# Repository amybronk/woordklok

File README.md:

# woordklok
het is een woordklok
 de dezine files moeten nog geupload worden

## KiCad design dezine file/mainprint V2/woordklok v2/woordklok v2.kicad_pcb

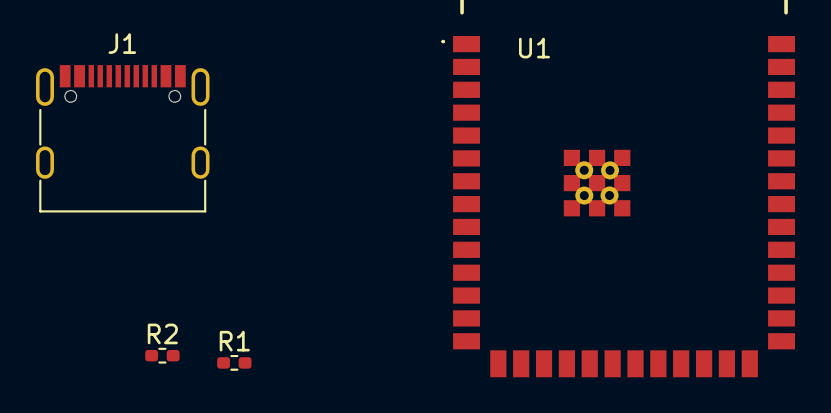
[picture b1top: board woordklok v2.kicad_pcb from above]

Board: 2 copper layers, 4 parts (0 on the bottom side), 6 nets, no tracks yet.

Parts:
J1: USB_C_Receptacle_USB2.0_16P; USB_C_Receptacle_G-Switch_GT-USB-7010ASV
R1, R2: 22R; R_0402_1005Metric_Pad0.72x0.64mm_HandSolder
U1: esp32-s3-wroom; ESP32S3WROOM1

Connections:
/USB1.D+: R2.1, U1.14 (IO20)
/USB1.D-: R1.1, U1.13 (IO19)
GND: J1.A1 (GND), J1.A12 (GND), J1.B1 (GND), J1.B12 (GND), J1.S1 (SHIELD), U1.1 (GND), U1.40 (GND), U1.41 (GND)
unnamed: J1.A4 (VBUS), J1.A9 (VBUS), J1.B4 (VBUS), J1.B9 (VBUS)
USB_N: J1.A7 (D-), J1.B7 (D-), R1.2
USB_P: J1.A6 (D+), J1.B6 (D+), R2.2

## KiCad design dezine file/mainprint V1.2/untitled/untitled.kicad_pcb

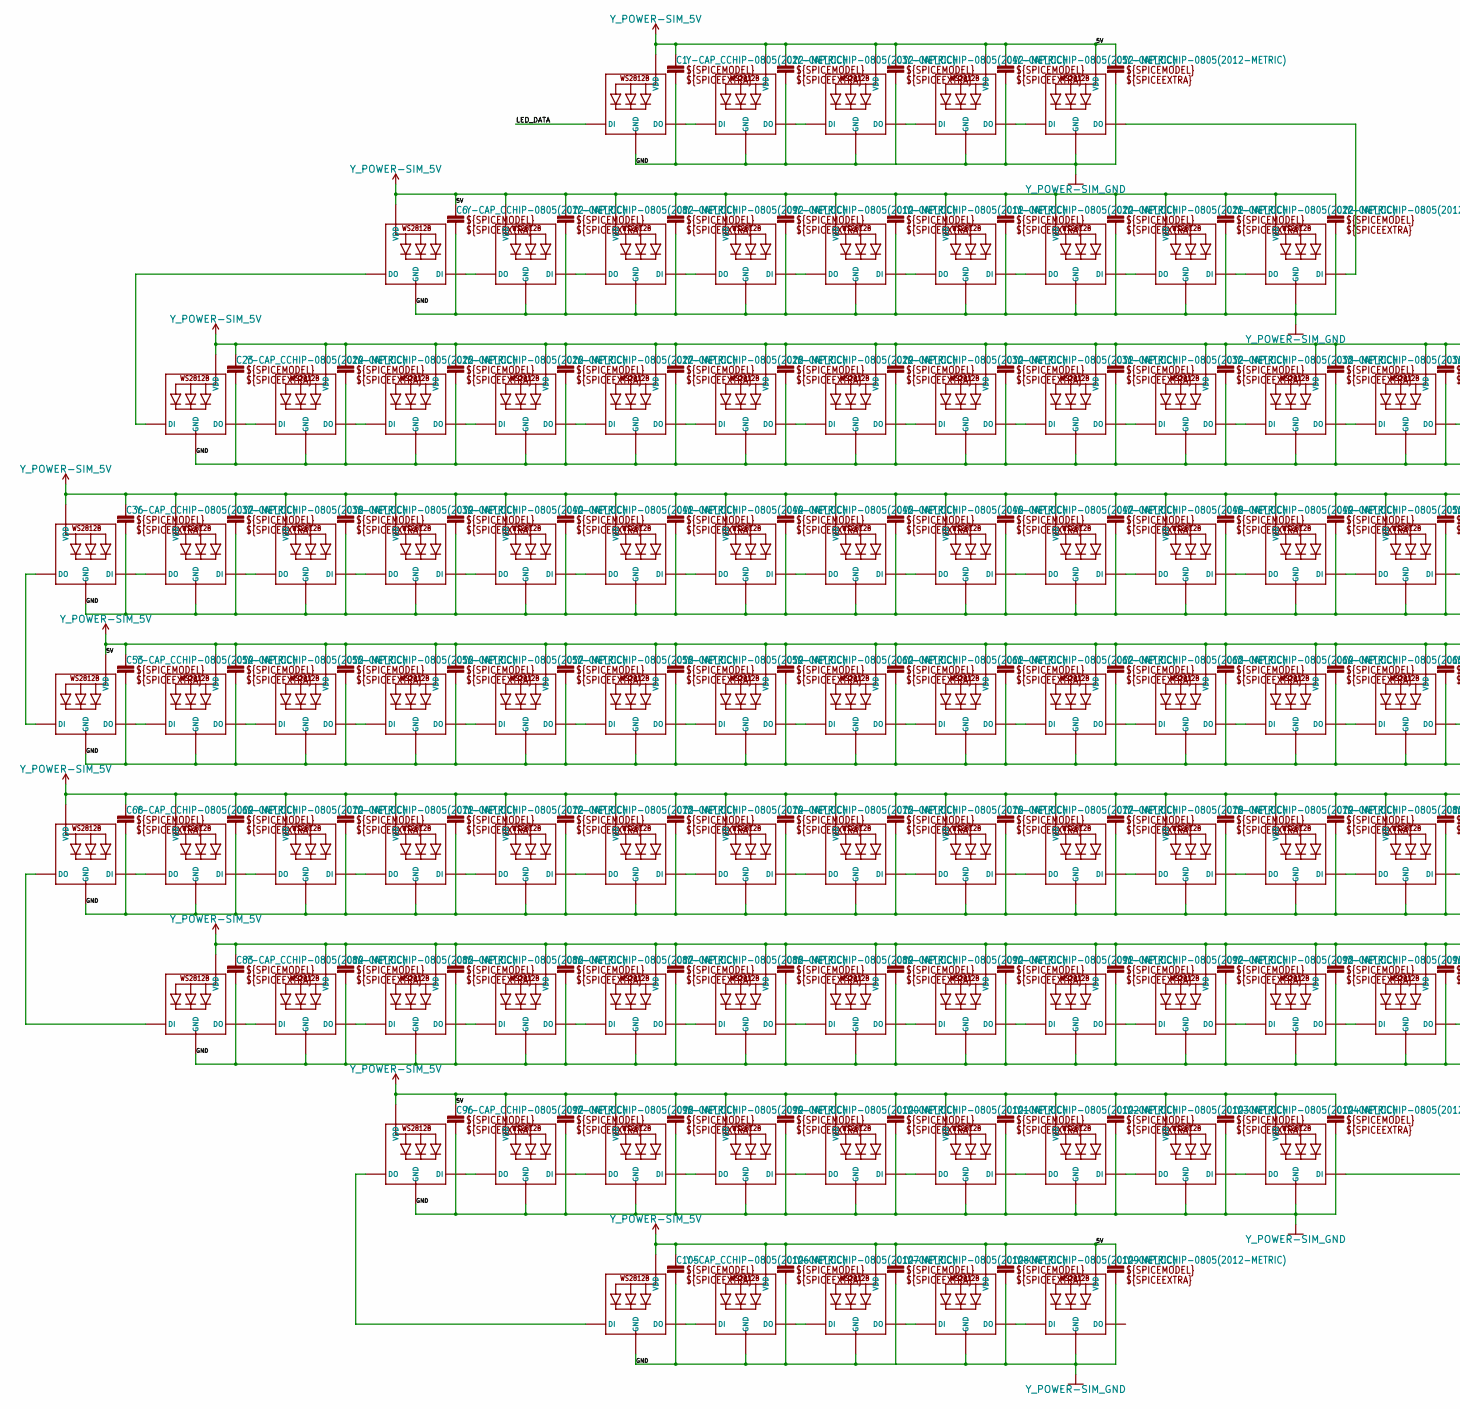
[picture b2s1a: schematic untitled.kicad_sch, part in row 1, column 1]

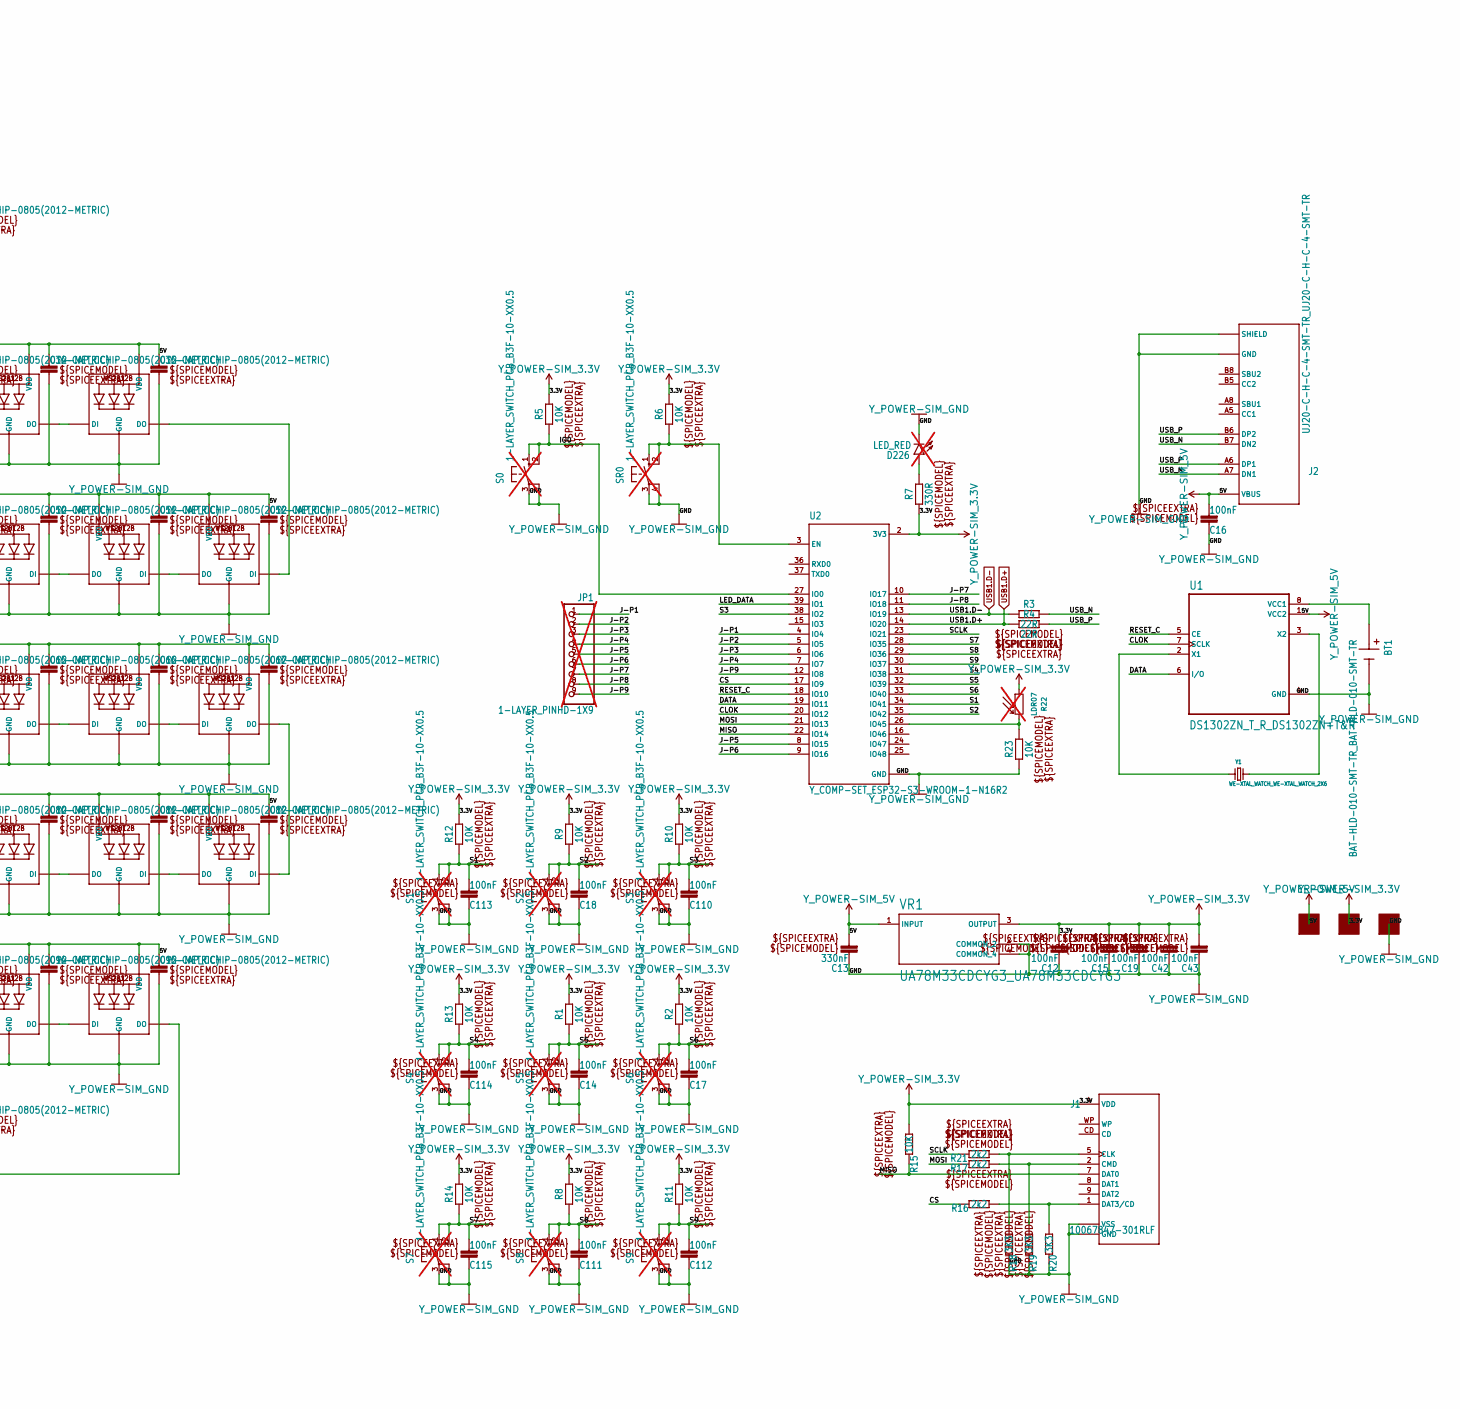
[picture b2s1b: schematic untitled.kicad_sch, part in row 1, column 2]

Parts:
BT1: BAT-HLD-010-SMT-TR_BAT-HLD-010-SMT-TR; BAT-HLD-010-SMT-TR_BAT_BAT-HLD-010-SMT-TR
C1, C2, C3, C4, C5, C6, C7, C8, C9, C10, C11, C20, C21, C22, C23, C24, C25, C26, C27, C28, C29, C30, C31, C32, C33, C34, C35, C36, C37, C38, C39, C40, C41, C44, C45, C46, C47, C48, C49, C50, C51, C52, C53, C54, C55, C56, C57, C58, C59, C60, C61, C62, C63, C64, C65, C66, C67, C68, C69, C70, C71, C72, C73, C74, C75, C76, C77, C78, C79, C80, C81, C82, C83, C84, C85, C86, C87, C88, C89, C90, C91, C92, C93, C94, C95, C96, C97, C98, C99, C100, C101, C102, C103, C104, C105, C106, C107, C108, C109: Y-CAP_CCHIP-0805(2012-METRIC); Y-CAP_CAPC2012X110
C12, C14, C15, C16, C17, C18, C19, C42, C43, C110, C111, C112, C113, C114, C115: 100nF; Y-CAP_CAPC2012X110
C13: 330nF; Y-CAP_CAPC2012X110
D226: LED_RED; 1-LAYER_LED5MM_R-ROC; not fitted
J1: 10067847-301RLF; AMPHENOL_10067847-301RLF
J2: UJ20-C-H-C-4-SMT-TR_UJ20-C-H-C-4-SMT-TR; UJ20-C-H-C-4-SMT-TR_CUI_UJ20-C-H-C-4-SMT-TR
JP1: 1-LAYER_PINHD-1X9; 1-LAYER_1X09; not fitted
LED1, LED2, LED3, LED4, LED5, LED6, LED7, LED8, LED9, LED10, LED11, LED12, LED13, LED14, LED15, LED16, LED17, LED18, LED19, LED20, LED21, LED22, LED23, LED24, LED25, LED26, LED27, LED28, LED29, LED30, LED31, LED32, LED33, LED34, LED35, LED36, LED37, LED38, LED39, LED40, LED41, LED42, LED43, LED44, LED45, LED46, LED47, LED48, LED49, LED50, LED51, LED52, LED53, LED54, LED55, LED56, LED57, LED58, LED59, LED60, LED61, LED62, LED63, LED64, LED65, LED66, LED67, LED68, LED69, LED70, LED71, LED72, LED73, LED74, LED75, LED76, LED77, LED78, LED79, LED80, LED81, LED82, LED83, LED84, LED85, LED86, LED87, LED88, LED89, LED90, LED91, LED92, LED93, LED94, LED95, LED96, LED97, LED98, LED99: WS2812B_WS2812B_5050N; WS2812B_WS2812B-NARROW
R1, R2, R5, R6, R8, R9, R10, R11, R12, R13, R14, R15, R23: 10K; Y-RES_RESC2012X65
R3, R4: 22R; Y-RES_RESC2012X65
R7: 330R; Y-RES_RESC2012X65
R16, R17, R21: 2k2; Y-RES_RESC2012X65
R18, R19, R20: 3K3; Y-RES_RESC2012X65
R22: LDR07; R_LDR_5.1x4.3mm_P3.4mm_Vertical; not fitted
S0, S1, S2, S3, S4, S5, S6, S7, S8, S9: 1-LAYER_SWITCH_PCB_B3F-10-XX0.5; 1-LAYER_B3F-10XXROC; not fitted
SR0: 1-LAYER_SWITCH_PCB_B3F-10-XX0.5; 1-LAYER_B3F-10XXROC; not fitted
U1: DS1302ZN_T_R_DS1302ZN+T&R; DS1302ZN_T_R_SOIC127P600X175-8N
U2: Y_COMP-SET_ESP32-S3-WROOM-1-N16R2; Y_COMP-SET_XCVR_ESP32-S3-WROOM-1-N16R2
U$1, U$2, U$3: Y_CONECTOR_POGOPAD2; Y_CONECTOR_POGOPAD_50
VR1: UA78M33CDCYG3_UA78M33CDCYG3; UA78M33CDCYG3_VREG_UA78M33CDCYG3
Y1: WE-XTAL_WATCH_WE-XTAL_WATCH_2X6; WE-XTAL_WATCH_WE-XTAL_WATCH-2X6

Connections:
/CLOK: U1.7 (SCLK), U2.20 (IO12)
/CS: R16.2, U2.17 (IO9)
/DATA: U1.6 (I/O), U2.19 (IO11)
/IO0: R5.1, S0.1 (S), S0.2 (S1), U2.27 (IO0)
/J-P1: JP1.1, U2.4 (IO4)
/J-P2: JP1.2, U2.5 (IO5)
/J-P3: JP1.3, U2.6 (IO6)
/J-P4: JP1.4, U2.7 (IO7)
/J-P5: JP1.5, U2.8 (IO15)
/J-P6: JP1.6, U2.9 (IO16)
/J-P7: JP1.7, U2.10 (IO17)
/J-P8: JP1.8, U2.11 (IO18)
/J-P9: JP1.9, U2.12 (IO8)
/LED_DATA: LED1.4-DIN (DI), U2.39 (IO1)
/MISO: J1.7 (DAT0), R15.2, U2.22 (IO14)
/MOSI: R17.2, U2.21 (IO13)
/RESET_C: U1.5 (CE), U2.18 (IO10)
/S1: C113.2, R12.1, S1.1 (S), S1.2 (S1), U2.34 (IO41)
/S2: C18.2, R9.1, S2.1 (S), S2.2 (S1), U2.35 (IO42)
/S3: C110.2, R10.1, S3.1 (S), S3.2 (S1), U2.38 (IO2)
/S4: C114.2, R13.1, S4.1 (S), S4.2 (S1), U2.31 (IO38)
/S5: C14.2, R1.1, S5.1 (S), S5.2 (S1), U2.32 (IO39)
/S6: C17.2, R2.1, S6.1 (S), S6.2 (S1), U2.33 (IO40)
/S7: C115.2, R14.1, S7.1 (S), S7.2 (S1), U2.28 (IO35)
/S8: C111.2, R8.1, S8.1 (S), S8.2 (S1), U2.29 (IO36)
/S9: C112.2, R11.1, S9.1 (S), S9.2 (S1), U2.30 (IO37)
/SCLK: R21.2, U2.23 (IO21)
/USB_N: J2.A7 (DN1), J2.B7 (DN2), R3.2
/USB_P: J2.A6 (DP1), J2.B6 (DP2), R4.2
unnamed: J1.5 (CLK), R18.1, R21.1
unnamed: J1.2 (CMD), R17.1, R19.1
unnamed: J1.1 (DAT3/CD), R16.1, R20.1
unnamed: LED1.2-DOUT (DO), LED2.4-DIN (DI)
unnamed: LED2.2-DOUT (DO), LED3.4-DIN (DI)
unnamed: LED3.2-DOUT (DO), LED4.4-DIN (DI)
unnamed: LED4.2-DOUT (DO), LED5.4-DIN (DI)
unnamed: LED6.4-DIN (DI), LED7.2-DOUT (DO)
unnamed: LED7.4-DIN (DI), LED8.2-DOUT (DO)
unnamed: LED8.4-DIN (DI), LED9.2-DOUT (DO)
unnamed: LED10.4-DIN (DI), LED11.2-DOUT (DO)
unnamed: LED9.4-DIN (DI), LED10.2-DOUT (DO)
unnamed: LED11.4-DIN (DI), LED12.2-DOUT (DO)
unnamed: LED12.4-DIN (DI), LED13.2-DOUT (DO)
unnamed: LED13.4-DIN (DI), LED14.2-DOUT (DO)
unnamed: LED5.2-DOUT (DO), LED14.4-DIN (DI)
unnamed: LED15.4-DIN (DI), LED24.2-DOUT (DO)
unnamed: LED15.2-DOUT (DO), LED26.4-DIN (DI)
unnamed: LED16.4-DIN (DI), LED17.2-DOUT (DO)
unnamed: LED16.2-DOUT (DO), LED27.4-DIN (DI)
unnamed: LED17.4-DIN (DI), LED18.2-DOUT (DO)
unnamed: LED18.4-DIN (DI), LED19.2-DOUT (DO)
unnamed: LED19.4-DIN (DI), LED25.2-DOUT (DO)
unnamed: LED6.2-DOUT (DO), LED20.4-DIN (DI)
unnamed: LED20.2-DOUT (DO), LED21.4-DIN (DI)
unnamed: LED21.2-DOUT (DO), LED22.4-DIN (DI)
unnamed: LED22.2-DOUT (DO), LED23.4-DIN (DI)
unnamed: LED23.2-DOUT (DO), LED24.4-DIN (DI)
unnamed: LED25.4-DIN (DI), LED45.2-DOUT (DO)
unnamed: LED26.2-DOUT (DO), LED32.4-DIN (DI)
unnamed: LED27.2-DOUT (DO), LED28.4-DIN (DI)
unnamed: LED28.2-DOUT (DO), LED29.4-DIN (DI)
unnamed: LED29.2-DOUT (DO), LED30.4-DIN (DI)
unnamed: LED30.2-DOUT (DO), LED31.4-DIN (DI)
unnamed: LED31.2-DOUT (DO), LED50.4-DIN (DI)
unnamed: LED32.2-DOUT (DO), LED38.4-DIN (DI)
unnamed: LED33.4-DIN (DI), LED34.2-DOUT (DO)
unnamed: LED33.2-DOUT (DO), LED73.4-DIN (DI)
unnamed: LED34.4-DIN (DI), LED35.2-DOUT (DO)
unnamed: LED35.4-DIN (DI), LED36.2-DOUT (DO)
unnamed: LED36.4-DIN (DI), LED37.2-DOUT (DO)
unnamed: LED37.4-DIN (DI), LED39.2-DOUT (DO)
unnamed: LED38.2-DOUT (DO), LED44.4-DIN (DI)
unnamed: LED39.4-DIN (DI), LED40.2-DOUT (DO)
unnamed: LED40.4-DIN (DI), LED41.2-DOUT (DO)
unnamed: LED41.4-DIN (DI), LED42.2-DOUT (DO)
unnamed: LED42.4-DIN (DI), LED43.2-DOUT (DO)
unnamed: LED43.4-DIN (DI), LED58.2-DOUT (DO)
unnamed: LED44.2-DOUT (DO), LED55.4-DIN (DI)
unnamed: LED45.4-DIN (DI), LED46.2-DOUT (DO)
unnamed: LED46.4-DIN (DI), LED47.2-DOUT (DO)
unnamed: LED47.4-DIN (DI), LED48.2-DOUT (DO)
unnamed: LED48.4-DIN (DI), LED49.2-DOUT (DO)
unnamed: LED49.4-DIN (DI), LED60.2-DOUT (DO)
unnamed: LED50.2-DOUT (DO), LED51.4-DIN (DI)
unnamed: LED51.2-DOUT (DO), LED52.4-DIN (DI)
unnamed: LED52.2-DOUT (DO), LED53.4-DIN (DI)
unnamed: LED53.2-DOUT (DO), LED54.4-DIN (DI)
unnamed: LED54.2-DOUT (DO), LED65.4-DIN (DI)
unnamed: LED55.2-DOUT (DO), LED56.4-DIN (DI)
unnamed: LED56.2-DOUT (DO), LED57.4-DIN (DI)
unnamed: LED57.2-DOUT (DO), LED69.4-DIN (DI)
unnamed: LED58.4-DIN (DI), LED59.2-DOUT (DO)
unnamed: LED59.4-DIN (DI), LED63.2-DOUT (DO)
unnamed: LED60.4-DIN (DI), LED61.2-DOUT (DO)
unnamed: LED61.4-DIN (DI), LED62.2-DOUT (DO)
unnamed: LED62.4-DIN (DI), LED68.2-DOUT (DO)
unnamed: LED63.4-DIN (DI), LED64.2-DOUT (DO)
unnamed: LED64.4-DIN (DI), LED72.2-DOUT (DO)
unnamed: LED65.2-DOUT (DO), LED66.4-DIN (DI)
unnamed: LED66.2-DOUT (DO), LED67.4-DIN (DI)
unnamed: LED67.2-DOUT (DO), LED70.4-DIN (DI)
unnamed: LED68.4-DIN (DI), LED69.2-DOUT (DO)
unnamed: LED70.2-DOUT (DO), LED71.4-DIN (DI)
unnamed: LED71.2-DOUT (DO), LED72.4-DIN (DI)
unnamed: LED73.2-DOUT (DO), LED74.4-DIN (DI)
unnamed: LED74.2-DOUT (DO), LED75.4-DIN (DI)
unnamed: LED75.2-DOUT (DO), LED76.4-DIN (DI)
unnamed: LED76.2-DOUT (DO), LED77.4-DIN (DI)
unnamed: LED77.2-DOUT (DO), LED78.4-DIN (DI)
unnamed: LED78.2-DOUT (DO), LED79.4-DIN (DI)
unnamed: LED79.2-DOUT (DO), LED80.4-DIN (DI)
unnamed: LED80.2-DOUT (DO), LED81.4-DIN (DI)
unnamed: LED81.2-DOUT (DO), LED82.4-DIN (DI)
unnamed: LED82.2-DOUT (DO), LED83.4-DIN (DI)
unnamed: LED83.2-DOUT (DO), LED84.4-DIN (DI)
unnamed: LED84.2-DOUT (DO), LED85.4-DIN (DI)
unnamed: LED85.2-DOUT (DO), LED94.4-DIN (DI)
unnamed: LED86.4-DIN (DI), LED87.2-DOUT (DO)
unnamed: LED86.2-DOUT (DO), LED95.4-DIN (DI)
unnamed: LED87.4-DIN (DI), LED88.2-DOUT (DO)
unnamed: LED88.4-DIN (DI), LED89.2-DOUT (DO)
unnamed: LED89.4-DIN (DI), LED90.2-DOUT (DO)
unnamed: LED90.4-DIN (DI), LED91.2-DOUT (DO)
unnamed: LED91.4-DIN (DI), LED92.2-DOUT (DO)
unnamed: LED92.4-DIN (DI), LED93.2-DOUT (DO)
unnamed: LED93.4-DIN (DI), LED94.2-DOUT (DO)
unnamed: LED95.2-DOUT (DO), LED96.4-DIN (DI)
unnamed: LED96.2-DOUT (DO), LED97.4-DIN (DI)
unnamed: LED97.2-DOUT (DO), LED98.4-DIN (DI)
unnamed: LED98.2-DOUT (DO), LED99.4-DIN (DI)
unnamed: R6.1, SR0.1 (S), SR0.2 (S1), U2.3 (EN)
unnamed: BT1.P, U1.8 (VCC1)
unnamed: U1.2 (X1), Y1.1
unnamed: U1.3 (X2), Y1.2
unnamed: R22.2, R23.2, U2.26 (IO45)
USB1.D+: R4.1, U2.14 (IO20)
USB1.D-: R3.1, U2.13 (IO19)
Y_POWER-SIM_3.3V: C12.2, C15.2, C19.2, C42.2, C43.2, J1.4 (VDD), R1.2, R2.2, R5.2, R6.2, R7.1, R8.2, R9.2, R10.2, R11.2, R12.2, R13.2, R14.2, R15.1, R22.1, U2.2 (3V3), U$1.P$1, VR1.3 (OUTPUT)
Y_POWER-SIM_5V: C1.1, C2.1, C3.1, C4.1, C5.1, C6.1, C7.1, C8.1, C9.1, C10.1, C11.1, C13.2, C16.2, C20.1, C21.1, C22.1, C23.1, C24.1, C25.1, C26.1, C27.1, C28.1, C29.1, C30.1, C31.1, C32.1, C33.1, C34.1, C35.1, C36.1, C37.1, C38.1, C39.1, C40.1, C41.1, C44.1, C45.1, C46.1, C47.1, C48.1, C49.1, C50.1, C51.1, C52.1, C53.1, C54.1, C55.1, C56.1, C57.1, C58.1, C59.1, C60.1, C61.1, C62.1, C63.1, C64.1, C65.1, C66.1, C67.1, C68.1, C69.1, C70.1, C71.1, C72.1, C73.1, C74.1, C75.1, C76.1, C77.1, C78.1, C79.1, C80.1, C81.1, C82.1, C83.1, C84.1, C85.1, C86.1, C87.1, C88.1, C89.1, C90.1, C91.1, C92.1, C93.1, C94.1, C95.1, C96.1, C97.1, C98.1, C99.1, C100.1, C101.1, C102.1, C103.1, C104.1, C105.1, C106.1, C107.1, C108.1, C109.1, J2.A4_B9 (VBUS), J2.A9_B4 (VBUS), LED1.1-VDD (VDD), LED2.1-VDD (VDD), LED3.1-VDD (VDD), LED4.1-VDD (VDD), LED5.1-VDD (VDD), LED6.1-VDD (VDD), LED7.1-VDD (VDD), LED8.1-VDD (VDD), LED9.1-VDD (VDD), LED10.1-VDD (VDD), LED11.1-VDD (VDD), LED12.1-VDD (VDD), LED13.1-VDD (VDD), LED14.1-VDD (VDD), LED15.1-VDD (VDD), LED16.1-VDD (VDD), LED17.1-VDD (VDD), LED18.1-VDD (VDD), LED19.1-VDD (VDD), LED20.1-VDD (VDD), LED21.1-VDD (VDD), LED22.1-VDD (VDD), LED23.1-VDD (VDD), LED24.1-VDD (VDD), LED25.1-VDD (VDD), LED26.1-VDD (VDD), LED27.1-VDD (VDD), LED28.1-VDD (VDD), LED29.1-VDD (VDD), LED30.1-VDD (VDD), LED31.1-VDD (VDD), LED32.1-VDD (VDD), LED33.1-VDD (VDD), LED34.1-VDD (VDD), LED35.1-VDD (VDD), LED36.1-VDD (VDD), LED37.1-VDD (VDD), LED38.1-VDD (VDD), LED39.1-VDD (VDD), LED40.1-VDD (VDD), LED41.1-VDD (VDD), LED42.1-VDD (VDD), LED43.1-VDD (VDD), LED44.1-VDD (VDD), LED45.1-VDD (VDD), LED46.1-VDD (VDD), LED47.1-VDD (VDD), LED48.1-VDD (VDD), LED49.1-VDD (VDD), LED50.1-VDD (VDD), LED51.1-VDD (VDD), LED52.1-VDD (VDD), LED53.1-VDD (VDD), LED54.1-VDD (VDD), LED55.1-VDD (VDD), LED56.1-VDD (VDD), LED57.1-VDD (VDD), LED58.1-VDD (VDD), LED59.1-VDD (VDD), LED60.1-VDD (VDD), LED61.1-VDD (VDD), LED62.1-VDD (VDD), LED63.1-VDD (VDD), LED64.1-VDD (VDD), LED65.1-VDD (VDD), LED66.1-VDD (VDD), LED67.1-VDD (VDD), LED68.1-VDD (VDD), LED69.1-VDD (VDD), LED70.1-VDD (VDD), LED71.1-VDD (VDD), LED72.1-VDD (VDD), LED73.1-VDD (VDD), LED74.1-VDD (VDD), LED75.1-VDD (VDD), LED76.1-VDD (VDD), LED77.1-VDD (VDD), LED78.1-VDD (VDD), LED79.1-VDD (VDD), LED80.1-VDD (VDD), LED81.1-VDD (VDD), LED82.1-VDD (VDD), LED83.1-VDD (VDD), LED84.1-VDD (VDD), LED85.1-VDD (VDD), LED86.1-VDD (VDD), LED87.1-VDD (VDD), LED88.1-VDD (VDD), LED89.1-VDD (VDD), LED90.1-VDD (VDD), LED91.1-VDD (VDD), LED92.1-VDD (VDD), LED93.1-VDD (VDD), LED94.1-VDD (VDD), LED95.1-VDD (VDD), LED96.1-VDD (VDD), LED97.1-VDD (VDD), LED98.1-VDD (VDD), LED99.1-VDD (VDD), U1.1 (VCC2), U$3.P$1, VR1.1 (INPUT)
Y_POWER-SIM_GND: BT1.N, C1.2, C2.2, C3.2, C4.2, C5.2, C6.2, C7.2, C8.2, C9.2, C10.2, C11.2, C12.1, C13.1, C14.1, C15.1, C16.1, C17.1, C18.1, C19.1, C20.2, C21.2, C22.2, C23.2, C24.2, C25.2, C26.2, C27.2, C28.2, C29.2, C30.2, C31.2, C32.2, C33.2, C34.2, C35.2, C36.2, C37.2, C38.2, C39.2, C40.2, C41.2, C42.1, C43.1, C44.2, C45.2, C46.2, C47.2, C48.2, C49.2, C50.2, C51.2, C52.2, C53.2, C54.2, C55.2, C56.2, C57.2, C58.2, C59.2, C60.2, C61.2, C62.2, C63.2, C64.2, C65.2, C66.2, C67.2, C68.2, C69.2, C70.2, C71.2, C72.2, C73.2, C74.2, C75.2, C76.2, C77.2, C78.2, C79.2, C80.2, C81.2, C82.2, C83.2, C84.2, C85.2, C86.2, C87.2, C88.2, C89.2, C90.2, C91.2, C92.2, C93.2, C94.2, C95.2, C96.2, C97.2, C98.2, C99.2, C100.2, C101.2, C102.2, C103.2, C104.2, C105.2, C106.2, C107.2, C108.2, C109.2, C110.1, C111.1, C112.1, C113.1, C114.1, C115.1, D226.2 (C), J1.3 (VSS), J1.6 (VSS), J1.G1 (GND), J1.G2 (GND), J2.A1_B12 (GND), J2.A12_B1 (GND), J2.SH1 (SHIELD), J2.SH2 (SHIELD), J2.SH3 (SHIELD), J2.SH4 (SHIELD), LED1.3-GND (GND), LED2.3-GND (GND), LED3.3-GND (GND), LED4.3-GND (GND), LED5.3-GND (GND), LED6.3-GND (GND), LED7.3-GND (GND), LED8.3-GND (GND), LED9.3-GND (GND), LED10.3-GND (GND), LED11.3-GND (GND), LED12.3-GND (GND), LED13.3-GND (GND), LED14.3-GND (GND), LED15.3-GND (GND), LED16.3-GND (GND), LED17.3-GND (GND), LED18.3-GND (GND), LED19.3-GND (GND), LED20.3-GND (GND), LED21.3-GND (GND), LED22.3-GND (GND), LED23.3-GND (GND), LED24.3-GND (GND), LED25.3-GND (GND), LED26.3-GND (GND), LED27.3-GND (GND), LED28.3-GND (GND), LED29.3-GND (GND), LED30.3-GND (GND), LED31.3-GND (GND), LED32.3-GND (GND), LED33.3-GND (GND), LED34.3-GND (GND), LED35.3-GND (GND), LED36.3-GND (GND), LED37.3-GND (GND), LED38.3-GND (GND), LED39.3-GND (GND), LED40.3-GND (GND), LED41.3-GND (GND), LED42.3-GND (GND), LED43.3-GND (GND), LED44.3-GND (GND), LED45.3-GND (GND), LED46.3-GND (GND), LED47.3-GND (GND), LED48.3-GND (GND), LED49.3-GND (GND), LED50.3-GND (GND), LED51.3-GND (GND), LED52.3-GND (GND), LED53.3-GND (GND), LED54.3-GND (GND), LED55.3-GND (GND), LED56.3-GND (GND), LED57.3-GND (GND), LED58.3-GND (GND), LED59.3-GND (GND), LED60.3-GND (GND), LED61.3-GND (GND), LED62.3-GND (GND), LED63.3-GND (GND), LED64.3-GND (GND), LED65.3-GND (GND), LED66.3-GND (GND), LED67.3-GND (GND), LED68.3-GND (GND), LED69.3-GND (GND), LED70.3-GND (GND), LED71.3-GND (GND), LED72.3-GND (GND), LED73.3-GND (GND), LED74.3-GND (GND), LED75.3-GND (GND), LED76.3-GND (GND), LED77.3-GND (GND), LED78.3-GND (GND), LED79.3-GND (GND), LED80.3-GND (GND), LED81.3-GND (GND), LED82.3-GND (GND), LED83.3-GND (GND), LED84.3-GND (GND), LED85.3-GND (GND), LED86.3-GND (GND), LED87.3-GND (GND), LED88.3-GND (GND), LED89.3-GND (GND), LED90.3-GND (GND), LED91.3-GND (GND), LED92.3-GND (GND), LED93.3-GND (GND), LED94.3-GND (GND), LED95.3-GND (GND), LED96.3-GND (GND), LED97.3-GND (GND), LED98.3-GND (GND), LED99.3-GND (GND), R18.2, R19.2, R20.2, R23.1, S0.3, S0.4 (P1), S1.3, S1.4 (P1), S2.3, S2.4 (P1), S3.3, S3.4 (P1), S4.3, S4.4 (P1), S5.3, S5.4 (P1), S6.3, S6.4 (P1), S7.3, S7.4 (P1), S8.3, S8.4 (P1), S9.3, S9.4 (P1), SR0.3, SR0.4 (P1), U1.4 (GND), U2.1 (GND), U2.40 (GND), U2.41_1 (GND), U2.41_2 (GND), U2.41_3 (GND), U2.41_4 (GND), U2.41_5 (GND), U2.41_6 (GND), U2.41_7 (GND), U2.41_8 (GND), U2.41_9 (GND), U2.41_10 (GND), U2.41_11 (GND), U2.41_12 (GND), U2.41_13 (GND), U2.41_14 (GND), U2.41_15 (GND), U2.41_16 (GND), U2.41_17 (GND), U2.41_18 (GND), U2.41_19 (GND), U2.41_20 (GND), U2.41_21 (GND), U$2.P$1, VR1.2 (COMMON_2), VR1.4 (COMMON_4)

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
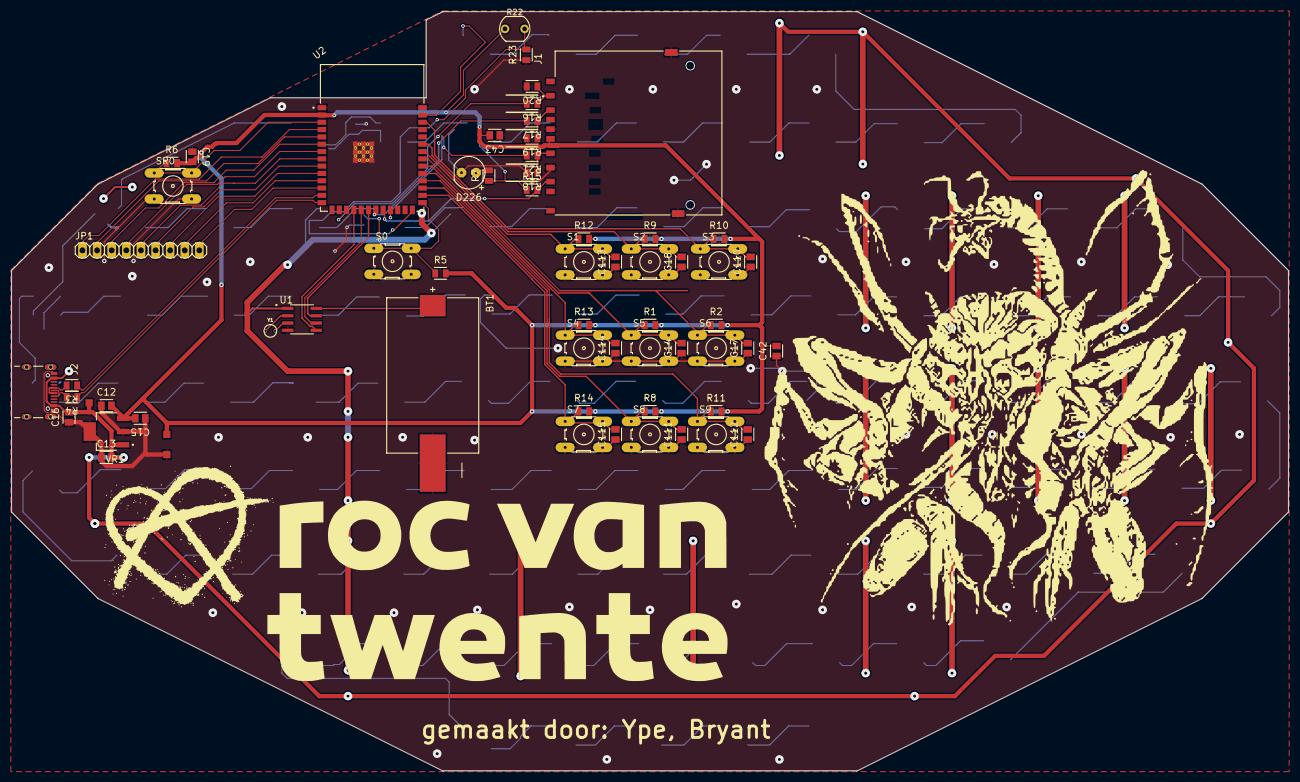
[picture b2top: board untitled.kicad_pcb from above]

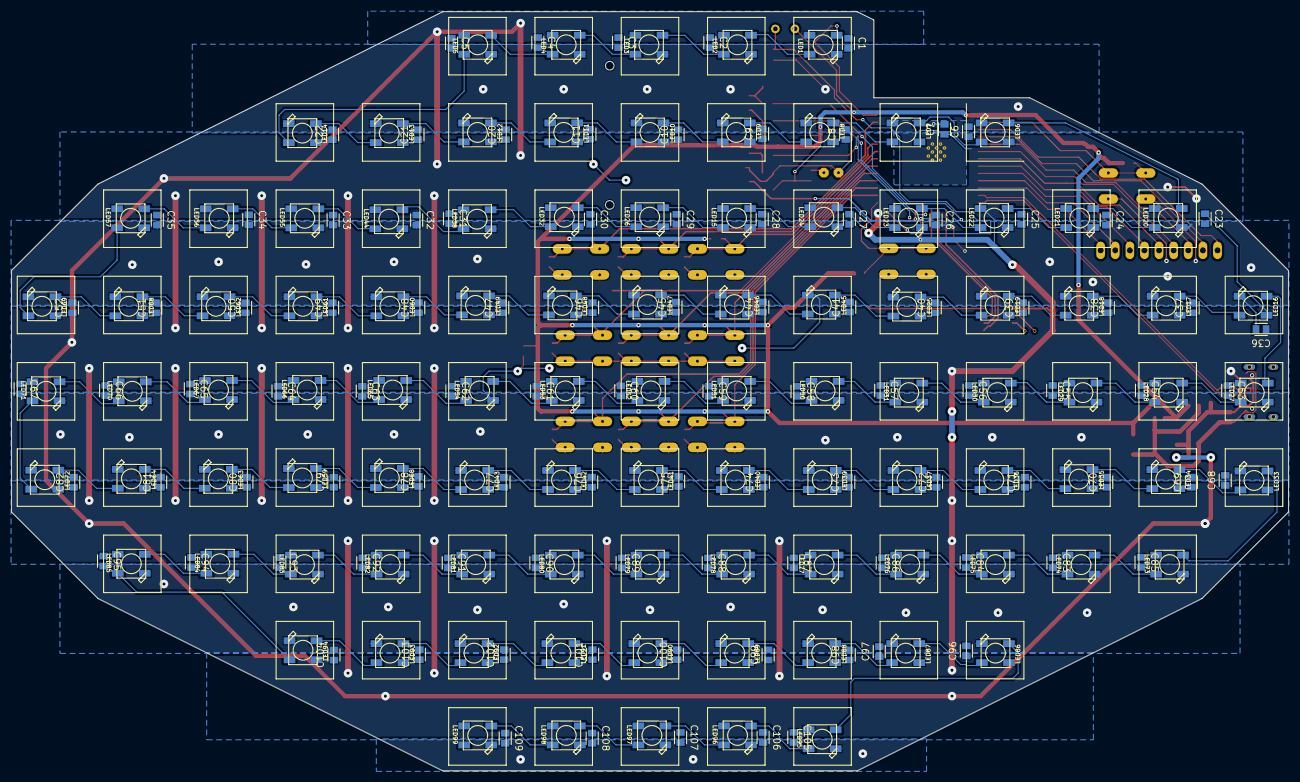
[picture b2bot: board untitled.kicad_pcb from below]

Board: 2 copper layers, 222.0 x 132.0 mm, 260 parts (198 on the bottom side), 140 nets.

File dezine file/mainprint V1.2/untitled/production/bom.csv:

Designator,Footprint,Quantity,Value,LCSC Part #
BT1,BAT-HLD-010-SMT-TR_BAT_BAT-HLD-010-SMT-TR,1,BAT-HLD-010-SMT-TR_BAT-HLD-010-SMT-TR,
"C1, C10, C100, C101, C102, C103, C104, C105, C106, C107, C108, C109, C11, C2, C20, C21, C22, C23, C24, C25, C26, C27, C28, C29, C3, C30, C31, C32, C33, C34, C35, C36, C37, C38, C39, C4, C40, C41, C44, C45, C46, C47, C48, C49, C5, C50, C51, C52, C53, C54, C55, C56, C57, C58, C59, C6, C60, C61, C62, C63, C64, C65, C66, C67, C68, C69, C7, C70, C71, C72, C73, C74, C75, C76, C77, C78, C79, C8, C80, C81, C82, C83, C84, C85, C86, C87, C88, C89, C9, C90, C91, C92, C93, C94, C95, C96, C97, C98, C99",Y-CAP_CAPC2012X110,99,Y-CAP_CCHIP-0805(2012-METRIC),
"C110, C111, C112, C113, C114, C115, C12, C14, C15, C16, C17, C18, C19, C42, C43",Y-CAP_CAPC2012X110,15,100nF,
C13,Y-CAP_CAPC2012X110,1,330nF,
D226,1-LAYER_LED5MM_R-ROC,1,LED_RED,
J1,AMPHENOL_10067847-301RLF,1,10067847-301RLF,
J2,UJ20-C-H-C-4-SMT-TR_CUI_UJ20-C-H-C-4-SMT-TR,1,UJ20-C-H-C-4-SMT-TR_UJ20-C-H-C-4-SMT-TR,
JP1,1-LAYER_1X09,1,1-LAYER_PINHD-1X9,
"LED1, LED10, LED11, LED12, LED13, LED14, LED15, LED16, LED17, LED18, LED19, LED2, LED20, LED21, LED22, LED23, LED24, LED25, LED26, LED27, LED28, LED29, LED3, LED30, LED31, LED32, LED33, LED34, LED35, LED36, LED37, LED38, LED39, LED4, LED40, LED41, LED42, LED43, LED44, LED45, LED46, LED47, LED48, LED49, LED5, LED50, LED51, LED52, LED53, LED54, LED55, LED56, LED57, LED58, LED59, LED6, LED60, LED61, LED62, LED63, LED64, LED65, LED66, LED67, LED68, LED69, LED7, LED70, LED71, LED72, LED73, LED74, LED75, LED76, LED77, LED78, LED79, LED8, LED80, LED81, LED82, LED83, LED84, LED85, LED86, LED87, LED88, LED89, LED9, LED90, LED91, LED92, LED93, LED94, LED95, LED96, LED97, LED98, LED99",WS2812B_WS2812B-NARROW,99,WS2812B_WS2812B_5050N,
"R1, R10, R11, R12, R13, R14, R15, R2, R23, R5, R6, R8, R9",Y-RES_RESC2012X65,13,10K,
"R16, R17, R21",Y-RES_RESC2012X65,3,2k2,
"R18, R19, R20",Y-RES_RESC2012X65,3,3K3,
R22,R_LDR_5.1x4.3mm_P3.4mm_Vertical,1,LDR07,
"R3, R4",Y-RES_RESC2012X65,2,22R,
R7,Y-RES_RESC2012X65,1,330R,
"S0, S1, S2, S3, S4, S5, S6, S7, S8, S9, SR0",1-LAYER_B3F-10XXROC,11,1-LAYER_SWITCH_PCB_B3F-10-XX0.5,
U1,DS1302ZN_T_R_SOIC127P600X175-8N,1,DS1302ZN_T_R_DS1302ZN+T&R,
U2,Y_COMP-SET_XCVR_ESP32-S3-WROOM-1-N16R2,1,Y_COMP-SET_ESP32-S3-WROOM-1-N16R2,
VR1,UA78M33CDCYG3_VREG_UA78M33CDCYG3,1,UA78M33CDCYG3_UA78M33CDCYG3,
Y1,WE-XTAL_WATCH_WE-XTAL_WATCH-2X6,1,WE-XTAL_WATCH_WE-XTAL_WATCH_2X6,

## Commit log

2025-05-20 print V1.2 + behuizing V1
    versie 1.2 van de printplaat en de behuizingis nu aanwezig
2025-05-20 1.2.1
    building v2
2025-12-14 1.2.2
